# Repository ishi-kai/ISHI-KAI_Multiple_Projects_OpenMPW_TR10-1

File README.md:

# ISHI会版OpenMPW TR10-1について
これは、[ISHI会版OpenMPW TR10-1](https://ishi-kai.org/openmpw/shuttle/tr10/2024/10/15/shuttle_ISHI-Kai_OpenMPW-TR10-1_start.html)にみんなで相乗りしたxschemによる回路図とklayoutによるレイアアウト置き場です。

## みんなの[相乗りチップ](Submitted/all_members_layout.gds)
- 
- 
- 

### 相乗りチップのラベル
- 緑枠  
-- DCDC回路  
- オレンジ枠  
-- 初めてのInverter回路  
- 紫枠  
-- 初めてのInverter回路だけどピン不足によりレイアアウト配置のみ  

### WSL Image
上記の回路図やシミュレーション、レイアウト、DRC、LVSを実行するための環境をセットアップしたWSLイメージを用意しています。

- [WSL Image](https://www.noritsuna.jp/download/ubuntu2204_TR10-1.tar.xz)
    - ID: ishikai
    - Pass: ishikai

#### Installing WSL Images
`wsl --import-in-place ubuntu2204_TR10-1 .\ubuntu2204_TR10-1\ext4.vhdx`

起動には"ubuntu2204_TR10-1.lnk"をご利用ください。  

#### Deleting WSL Images
イメージも削除されるので注意してください。    

`wsl --unregister ubuntu2204_TR10-1`

# 参加者リスト
- [dokunira](https://github.com/dokunira/inverter_layout)
- [f0r3st](https://github.com/foorests/inverter_ISHI)
- [hiro-ogawa](https://github.com/hiro-ogawa/ishi-kai-OpenMPW-TR10-1)
- [hyumanase](https://github.com/hyumanase/inverter)
- [matsumoto325](https://github.com/matsumoto325/ISHI-Kai-commit/)
- [monmonmon](https://github.com/monmonmon/ishi-20241027)
- [tomoya_nonymous](https://github.com/tomoyanonymous/20241027_ishikai_inverter)
- [xian_DIY](https://github.com/ugeugeHigh/ISHI_xian_first)
- [masahiro](https://github.com/pochiMasahiro/inverter_masahiro)
- [lufe](https://github.com/1uf3/)
- [noritsuna](https://github.com/noritsuna/)
- [sebasu](https://github.com/sebasu-semi/)
- [akapochi](https://github.com/akahoshi0502/)

## 各種リスト
- [ピンリスト](docs/pin_list.pdf)

# 参加者のデザイン
## [dokunira](https://github.com/dokunira/inverter_layout)：Inverter回路
### MOSのパラメータ
| | ゲート幅 w (μm) | ゲート長 l (μm) |
|----|----|----|
|PMOS| 4 | 1 |
|NMOS| 2 | 1 |

### 感想
以前からオープンソースのレイアウトソフト「KLayout」で設計を行いたいと思っていましたが、なかなか取り組む機会がありませんでした。今回は教えていただきながら進めたことで、短時間で設計を完了することができました。Design Rules Check (DRC) や xschemとの連携による Layout Versus Schematic (LVS) などのレイアウト検証も行え、大変満足しています。ありがとうございました。

- 
- 

#### Dラッチ回路
[初めての半導体設計・製造体験 for ISHI会のOpenMPW](https://ishikai.connpass.com/event/332952/) でインバータのレイアウト設計をした後、枠がもし余っていたらと思って作ったDラッチのレイアウトです。  

- 
- 
- 

## [f0r3st](https://github.com/foorests/inverter_ISHI)：Inverter回路
### 感想
アナログ回路について、教科書で仕組みやいくつかの回路を読んだりはしていたのですが、具体的な実装方法が分からなかったので今回のイベントに参加しました。  
xschemやklayoutを使って実際に回路図やレイアウトパターンを作るのが楽しかったです。ありがとうございました！  

- 
- 

## [hiro-ogawa](https://github.com/hiro-ogawa/ishi-kai-OpenMPW-TR10-1)：Inverter回路
- 環境構築
  - [セットアップスクリプト](https://github.com/ishi-kai/OpenRule1umPDK_setupEDA)
  - セットアップスクリプトの中身を確認したら、環境構築をガリガリやっているので、怖くなって専用PCを用意して、OSをクリーンインストール
  - Ubuntu 22.04.5 をセットアップ

```bash
sudo apt update
sudo apt upgrade -y
sudo apt install -y git

git clone git@github.com:ishi-kai/OpenRule1umPDK_setupEDA.git

cd OpenRule1umPDK_setupEDA
bash ./eda-setup.sh
bash ./pdk_TR-setup.sh
```

- 使ったツール
  - xschem
  - ngspice
  - klayout

### 設計情報

- Pch FET
  - W: 60um
  - L: 10um
- Nch FET
  - W: 20um
  - L: 10um

### シミュレーション結果
- 
- 

### 感想
- とりあえず最後まで完走できた
- 事前にOSのクリーンインストールをしておいたので、セットアップで問題が発生することがなくて良かった
- 半導体が自分で作れるって夢が広がる
- まぁそう言っても、すごいチップが作れるわけではないだろうけど・・・
- アナログ回路がわからんといけないのかな
- ツールが全体的に使いにくいのが残念

- 
- 

## [hyumanase](https://github.com/hyumanase/inverter)：Inverter回路
### 感想
[2024年10月イベント：初めての半導体設計・製造体験 for ISHI会のOpenMPW - connpass](https://ishikai.connpass.com/event/332952/)にて、初めての半導体設計をしました。難しくもたのしい時間でした。マウスと、めげない心と、皆さんの支えでなんとかなりました。ありがとうございました！  

- 
- 

## [matsumoto325](https://github.com/matsumoto325/ISHI-Kai-commit/)：Inverter回路
### 感想

* 会場について

     GMO Yours・フクラスの図書室で実施。施設はとてもきれいでした。  
     結構前に渋谷駅に着いたのですが、道がだいぶ変わっていて場所がわからない。下見をするかネットで良く調べてから行けばよかった。  
     少し遅れて到着したのでConnpassのフィードで連絡したのですが返信なし。たまたま中の人を一人知っていたので個別に連絡とって中に入れました。その節はお手数をおかけいたしました。

* 講習について

     環境の構築はスクリプト2発で出来て、時間はかかりましたが簡単に準備ができました。  
     資料は記載された内容のままに操作すれば出来るような書き方にはなっていなくて手間取りましたが、それがかえって理解度の向上につながった気がします。  

* xschem について

     操作感は慣れるまで少しかかったけど、なかなか良かった。ライブラリも事前にある程度用意してくれたのでさくさく進められましたが、自分で作らなければならない局面とかあるのかな？と思ったりしてますが、まだ調べてないです。どこかで拾ってインポートする方法とかも聞いてみたいです。

* klayout について

     もっと自動的に配置してくれるのかと思ったら以外に手動でしたｗ  
     1bit メモリに値する回路でもこんなに苦労するんだったら、大型のチップを焼くのにはどのくらい労力がかかるのだろうと思うと、いつも大型の LSI を設計してくれてる人たちに感謝の気持ちが湧いてきました。
     他の人のレイアウトを覗き見したら面白いレイアウトがあって、それも楽しめました。

- 
- 

## [monmonmon](https://github.com/monmonmon/ishi-20241027)：Inverter回路
### 感想
お絵描きツールの使い方を覚えた！  

- 
- 

## [tomoya_nonymous](https://github.com/tomoyanonymous/20241027_ishikai_inverter)：Inverter回路
### 感想
（感想）ほぼ初心者状態からのスタートでしたが一応作れたようなのでよかったです！  

- 
- 

## [xian_DIY](https://github.com/ugeugeHigh/ISHI_xian_first)：Inverter回路
### 感想
色々教えて頂きありがとうございました！  
初めてのツールという事もあり、開発環境の構築で躓いてしまいました。  
UbuntuをいれたLets noteを持って会場にいったのですが、何故か何度もフリーズしてしまい…  
当日は完走できませんでしたが、翌日自宅のメイン環境で再度環境構築をしてトライしてみたところ、なんとか最後までいきつけました。  
製造枠がまだ空いているとのことで頑張ってみたのですが、果たして間に合うか！？  

- 
- 

## [masahiro](https://github.com/pochiMasahiro/inverter_masahiro)：Inverter回路
### 感想
FET2個の単純なインバータでもIC設計を体験することができてとても楽しかったです。資料も充実していて独学でも困りませんでした。次はもう少し複雑な回路を設計してみようと思います。  

- 
- 

## DCDC_DOWN_Converter_4_ISHI-KAI_OpenMPW_TR10-1
ISHI-KAI_Multiple_Projects_OpenMPW_TR10-1 向けの降圧型DCDCコンバータ（12v->5V）です。

### Members 
- [lufe](https://github.com/1uf3/vco)
    - VCO担当
- [noritsuna](https://github.com/noritsuna/DCDC_DOWN_Converter_4_ISHI-KAI_OpenMPW_TR10-1)
    - 降圧部担当

### 内容
- 
- 
- 

### vco
[lufe](https://github.com/1uf3/vco)担当

#### xschem

##### inverter

##### buffer

##### vco

##### simulated vco hz

#### klayout

### 降圧部
#### xschem
- 

##### simulation
- 
- 

#### klayout
- 

### 降圧型DCDCコンバータ
#### xschem
- 

##### simulation
- 
- 

#### klayout
- 

## [昇圧型DCDCコンバータ](member_project/BoostDCDC/)
ISHI-KAI_Multiple_Projects_OpenMPW_TR10-1 向けの降圧型DCDCコンバータ（5V->12v）です。

### Members 
- [sebasu](https://github.com/sebasu-semi/)
    - 昇圧部担当
- [akapochi](https://github.com/akahoshi0502/)
    - 変換担当

### [昇圧型DCDCコンバータ](member_project/BoostDCDC/)
#### xschem
- 

#### ngspice
- 

#### klayout
-  

# 測定会
## 製造されたチップ
到着したチップです。  

- 
- 

チップ写真です。  

- 

## ボンディング
パッケージの選択肢がないため、自分たちでボンディングすることにしました。  
そこで、ボンディング用の基板をKiCADで設計して、製造しました。

-  

- [Bonding Board](kicad/OpenMPW-TR10/) 

### ボンディング用のボード
ボンディング用のボードにベアダイを張り付けた状態です。  
今回はUVレジンで貼り付けました。本来ならペースト半田で取り付けるのが良いかと思います。  

- 
- 
- 

### ボンディング作業風景
ボンディング中の風景です。  
みんな、初めてのため苦戦しました。  

- 
- 
- 

### ボンディング完了
無事にボンディングが完了したチップたちです。  

- 
- 
- 

### ポッティング完了
ボンディングしたチップをUVレジンでポッティングしました。  
思ったよりもきれいにポッティングできたようです。  
透明なため特性としては最悪ですが、観察用には最適でした。  

- 
- 
- 
- 
- 
- 

### ボンディング測定
ボンディングしたチップを測定しました。  
動作点が4Vとなりました。ちょっと高いため、ハズレかけていて接触抵抗が高い線が紛れていそうです。  

- 
- 

## パッケージされたチップ
東海理化さんのご厚意により「パッケージした場合のサンプル」としてISHI会のチップをパッケージしていただけました！  

- 

## 測定会風景
測定用の装置やセットアップ中の風景です。  

- 
- 

### インバーター測定
1kHz, 500kHz, 1MHzでどうさせてみた図です。  
500kHzくらいで限界って感じですね。  
まともに高速で動かすようには設計指定なので当然の結果ではありますが。高速に動かすには、Wを広くしたり、バランスよくP-FET,N-FETのL,Wを合わせる必要があります。  

- 
- 
- 

### Dラッチ測定
無事に使用通りに動きとなりました。  

- 

### 降圧型DCDCコンバータ
#### VCO部
- [回路図やレイアウト](https://github.com/ishi-kai/ISHI-KAI_Multiple_Projects_OpenMPW_TR10-1?tab=readme-ov-file#vco)  

##### VCOの動作確認
100kHz設計で33kHz動作となりました。  
なぜ、1/3の性能になってしまったかは、レイアウトしたときに出る寄生容量や測定用プローブなどの容量などにより、静電容量（キャパシタの大きさ）が増えるので、クロックが2～5倍くらい遅くなるのは普通だったりします。特に、この環境では容量の大きいプローブ（内部ではフェムトファラッドだがプローブはピコファラッドクラスとなる）があるので、妥当な結果と言える感じです。  
ですので、本当は、レイアウトしたときにPEX（寄生容量摘出）をするのが正攻法なのですが、OpenRule1umではPEX機能がないので仕方ないところですね。  

-    
-    
-    
-    

### 降圧部
- [回路図やレイアウト](https://github.com/ishi-kai/ISHI-KAI_Multiple_Projects_OpenMPW_TR10-1?tab=readme-ov-file#%E9%99%8D%E5%9C%A7%E9%83%A8)

##### 降圧部の動作確認
残念ながら、何も出力されていない状態です。手元に数種類しかコイル（インダクタ）が無いので、もうすこしいろいろなインダクタを入手して再実験してみたいと思います。VCOのクロックに合わせて、出力電圧が微増している現象が出ているので、もう少し大容量のインダクタやキャパシタに変えると動きそうな感じはしています。  

-

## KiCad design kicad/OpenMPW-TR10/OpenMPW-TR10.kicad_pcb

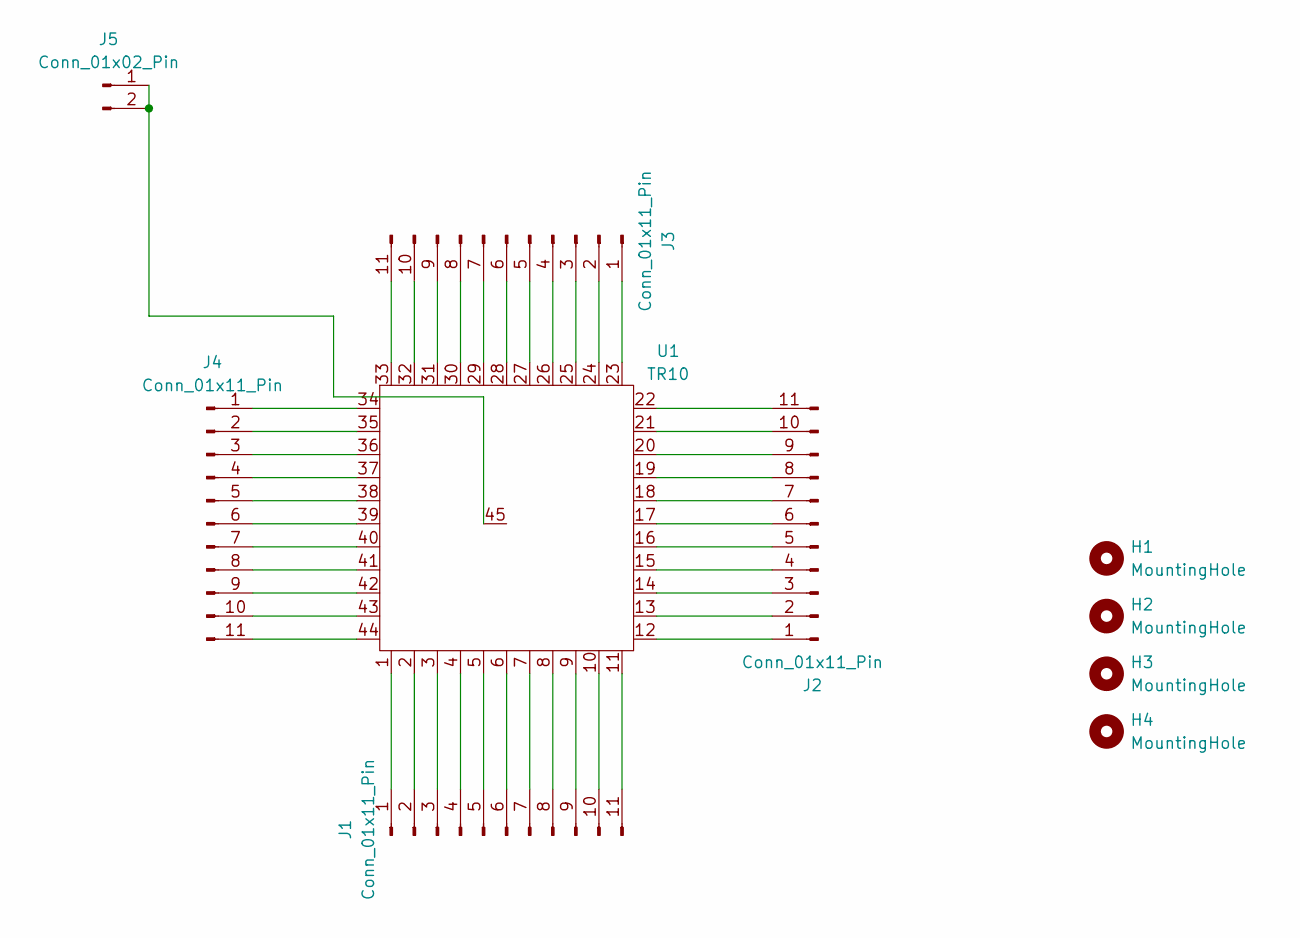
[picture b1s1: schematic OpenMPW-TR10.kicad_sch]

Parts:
H1, H2, H3, H4: MountingHole; MountingHole_3.2mm_M3
J1, J2, J3, J4: Conn_01x11_Pin; PinHeader_1x11_P2.54mm_Vertical
J5: Conn_01x02_Pin; PinHeader_1x02_P2.54mm_Vertical
U1: TR10; PAD-44_EP_5x5_Pitch0.2216mm

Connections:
unnamed: J1.1, U1.1
unnamed: J1.2, U1.2
unnamed: J1.3, U1.3
unnamed: J1.4, U1.4
unnamed: J1.5, U1.5
unnamed: J1.6, U1.6
unnamed: J1.7, U1.7
unnamed: J1.8, U1.8
unnamed: J1.9, U1.9
unnamed: J1.10, U1.10
unnamed: J1.11, U1.11
unnamed: J2.1, U1.12
unnamed: J2.2, U1.13
unnamed: J2.3, U1.14
unnamed: J2.4, U1.15
unnamed: J2.5, U1.16
unnamed: J2.6, U1.17
unnamed: J2.7, U1.18
unnamed: J2.8, U1.19
unnamed: J2.9, U1.20
unnamed: J2.10, U1.21
unnamed: J2.11, U1.22
unnamed: J3.1, U1.23
unnamed: J3.2, U1.24
unnamed: J3.3, U1.25
unnamed: J3.4, U1.26
unnamed: J3.5, U1.27
unnamed: J3.6, U1.28
unnamed: J3.7, U1.29
unnamed: J3.8, U1.30
unnamed: J3.9, U1.31
unnamed: J3.10, U1.32
unnamed: J3.11, U1.33
unnamed: J4.1, U1.34
unnamed: J4.2, U1.35
unnamed: J4.3, U1.36
unnamed: J4.4, U1.37
unnamed: J4.5, U1.38
unnamed: J4.6, U1.39
unnamed: J4.7, U1.40
unnamed: J4.8, U1.41
unnamed: J4.9, U1.42
unnamed: J4.10, U1.43
unnamed: J4.11, U1.44
unnamed: J5.1, J5.2, U1.45

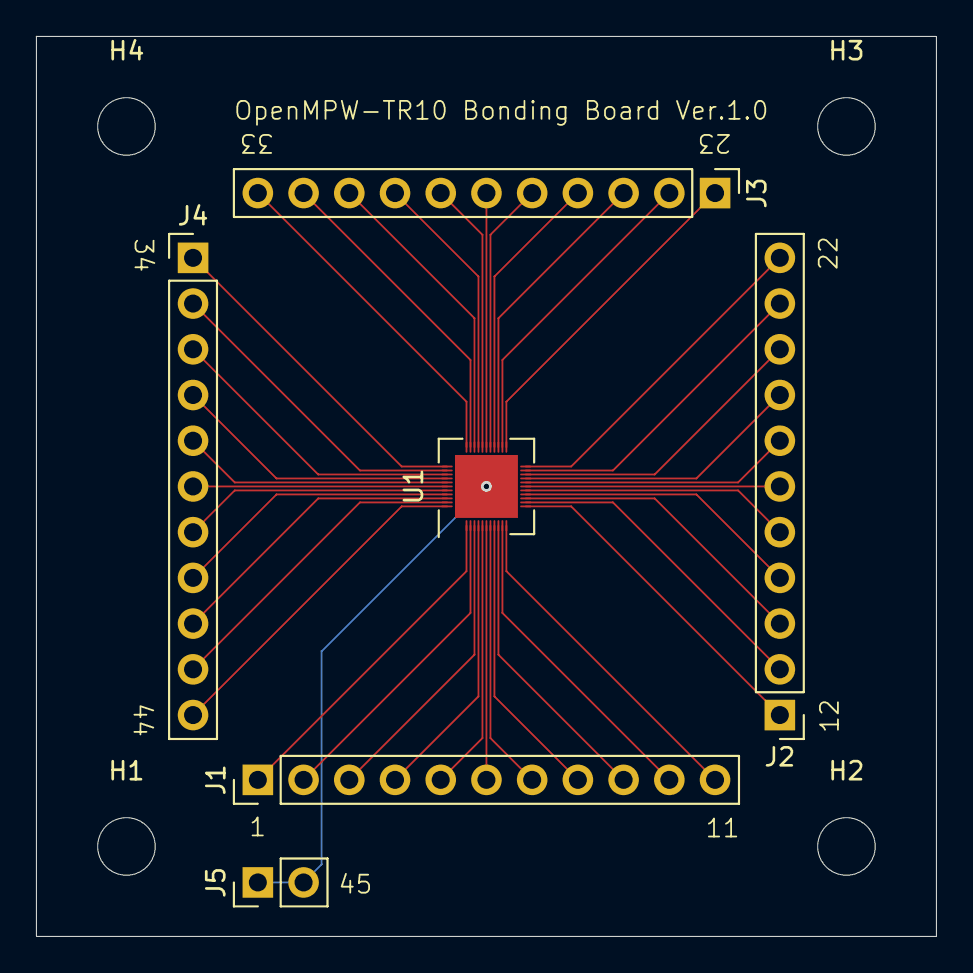
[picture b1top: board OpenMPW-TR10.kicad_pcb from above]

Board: 2 copper layers, 50.0 x 50.0 mm, 10 parts (0 on the bottom side), 45 nets.

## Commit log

2024-09-26 1st commit.
    1st commit.
2024-10-28 Update inverter_OR1.
    Update inverter_OR1.
2024-11-02 Add member's inverter.
    Add member's inverter.
2024-11-02 Typo.
    Typo.
2024-12-18 Add DCDC_DOWN&Submitted GDS.
    Add DCDC_DOWN&Submitted GDS.
2025-01-26 Boost修正2
2025-01-26 Boost_added
2025-01-27 Boost_delete
2025-01-27 Merge BoostDCDC.
    Merge BoostDCDC.
2025-01-27 add BoostDCDC.
2025-02-10 Add bonding board.
    Add bonding board.
2025-02-10 Convert minimum line width 3mil -> 4mil.
    Convert minimum line width 3mil -> 4mil.
2025-02-10 Add bonding board in README.
    Add bonding board in README.
2025-02-12 Support pad pitch 0.12mm.
    Support pad pitch 0.12mm.
2025-03-24 Fix ESD pin.
    Fix ESD pin.
2025-04-14 Add measure photos.
    Add measure photos.
2025-04-14 Fix typo.
    Fix typo.
2025-04-16 Rename jpg.
    Rename jpg.
2025-05-01 Add DCDC Down result.
    Add DCDC Down result.
2025-05-01 Rename.
    Rename.
2025-10-25 Delete DS_Store.
    Delete DS_Store.
2026-04-03 Update LICENSE
